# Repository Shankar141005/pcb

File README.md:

View this project on [CADLAB.io](https://cadlab.io/project/29191). 

# pcb

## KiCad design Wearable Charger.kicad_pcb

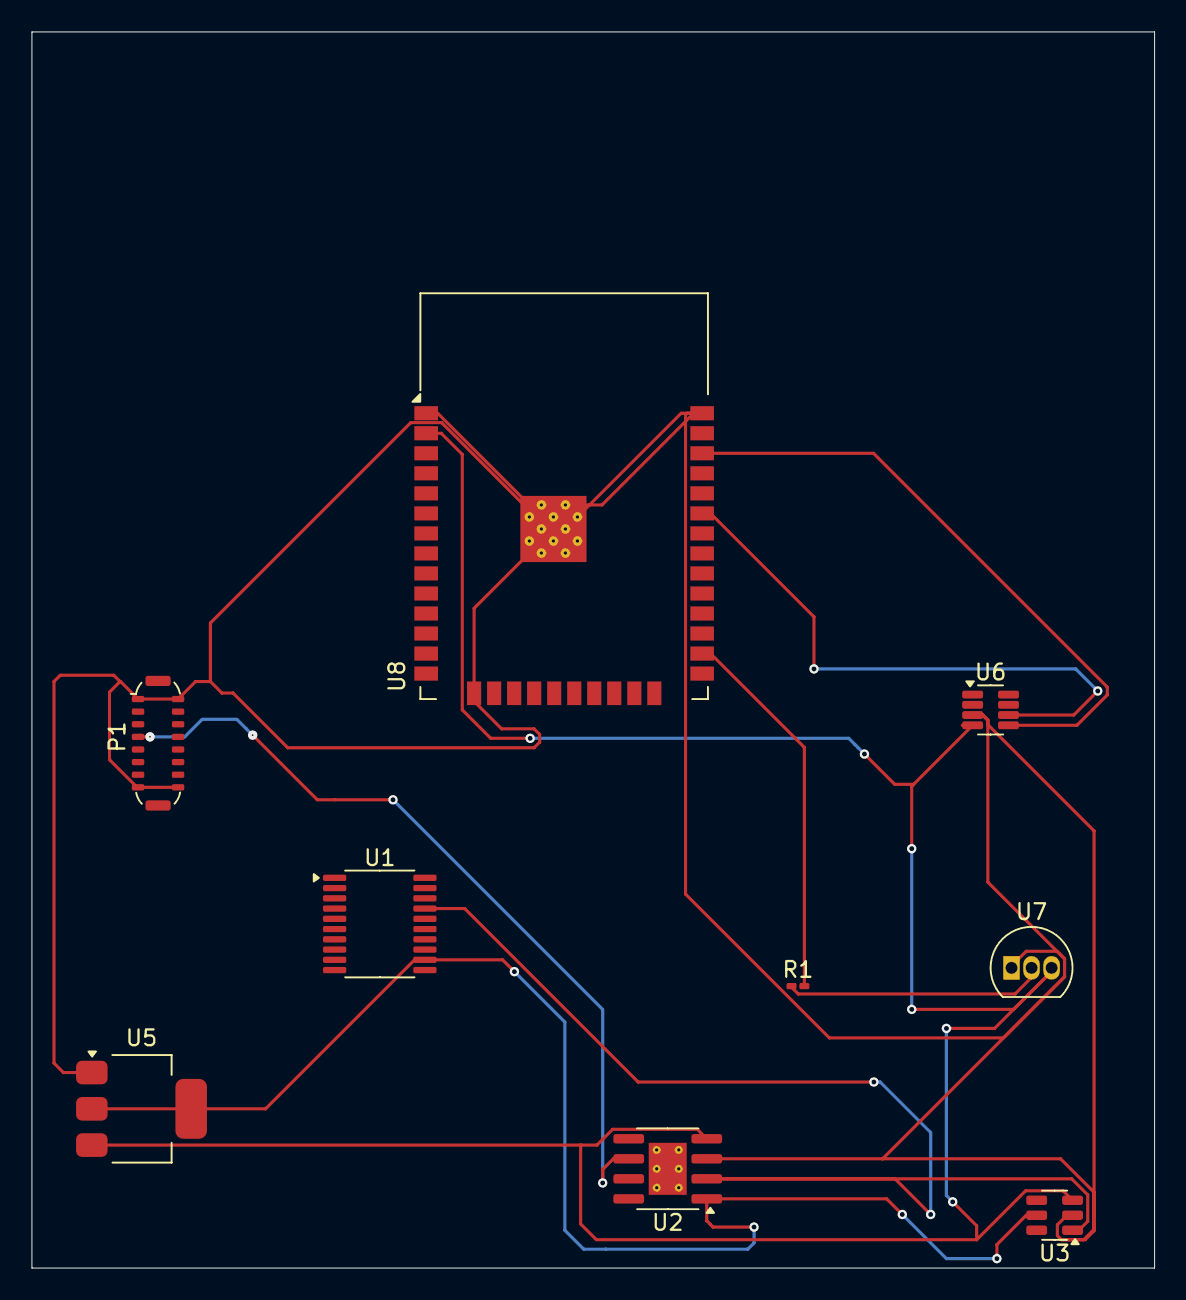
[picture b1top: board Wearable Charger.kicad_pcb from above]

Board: 2 copper layers, 71.2 x 78.4 mm, 9 parts (0 on the bottom side), 9 nets.

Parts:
P1: USB_C_Plug_USB2.0; USB_C_Plug_ShenzhenJingTuoJin_918-118A2021Y40002_Vertical
R1: R; R_0201_0603Metric_Pad0.64x0.40mm_HandSolder
U1: BQ76920PW; TSSOP-20_4.4x6.5mm_P0.65mm
U2: TP4056-42-ESOP8; SOIC-8-1EP_3.9x4.9mm_P1.27mm_EP2.41x3.3mm_ThermalVias
U3: MT3608; SOT-23-6
U5: AMS1117-3.3; SOT-223-3_TabPin2
U6: INA219BxDCN; SOT-23-8
U7: DS18B20; TO-92_Inline
U8: ESP32-WROOM-32

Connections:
/5v: U1.12 (VC5), U2.1 (TEMP), U3.5 (IN), U5.2 (VO)
/GPIO4: R1.2, U8.26 (IO4)
/GPIO21: U6.6 (SDA), U8.33 (IO21)
/GPIO22: U6.5 (SCL), U8.36 (IO22)
/IN: P1.A6 (D+), U2.6 (~STDBY)
/OUT: U1.17 (VC0), U2.2 (PROG), U3.1 (SW)
/gnd: P1.A1 (GND), P1.A12 (GND), P1.B1 (GND), P1.B12 (GND), U2.3 (GND), U3.2 (GND), U5.1 (GND), U6.3 (GND), U7.1 (GND), U8.1 (GND), U8.15 (GND), U8.38 (GND), U8.39 (GND)
/vcc: U2.4 (V_{CC}), U3.3 (FB), U5.3 (VI), U6.4 (VS), U7.3 (V_{DD}), U8.2 (VDD)
unnamed: R1.1, U7.2 (DQ)

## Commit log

2025-04-07 Backlink to CADLAB.io has been added.
